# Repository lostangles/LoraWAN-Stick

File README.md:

# LoraWAN-Stick
PCB combining Atmega32u4, MTK3339 GPS module, and RN2903 LoraWAN module.

<a href="https://oshpark.com/shared_projects/d93rjKRX"></img></a>

# Functionality
I wanted to make a single PCB that had some GPIO, communication interfaces, a module to transmit LoraWAN packets, and a way to get current location.  The LoraWAN stack is offloaded from the 32u4 and rests in a PIC microcontroller inside the RN2903.  This allows a simple interface of simply passing the payload from the 32u4 to the RN2903 without having to worry about the LoraWAN stack inside your project.

The LoraWAN-Stick incorporates the LiPo charging circuitry common to the Adafruit Feather line of dev boards, as well as follows the same pinout for attachment of Adafruit Featherwings.  Because both the RN2903 and GPS module use serial communications, serial communications with other nodes may be difficult; the GPS module uses the hardware UART, and communication to the RN2903 uses software serial.  From my experience, having multiple software serial interfaces tends to work in unexpected ways, and should probably be avoided without thorough testing.

# Pins
Pinout follows Adafruit Feather format as I wanted to be able to add compatability of Adafruit Featherwings to this project.
The 32u4 only has a single hardware UART, hard wired to the TX/RX of the GPS module.  These pins are broken out on the header.

The RN2903 is controlled by serial, but because the 32u4 has only a single UART, a software serial interface must be used.  The RN2903 is hardwired with its RX on pin 5 and TX on pin 10.  Reset for the RN2903 is hard wired to pin 6 and should be pulled high when not in reset state.  The RN2903 Pickit3 programming header is also broken out to update the firmware on the RN2903 directly.

#uC Info
The 32u4-AU microcontroller that I used here comes preconfigured to use the internal oscillator, thus the C7, C8, and XTAL pads can be left empty.  When configuring the microcontroller for the first time, it will not show up as a USB device until the bootloader has been flashed to it via ISP.  Once the bootloader has been flashed, it should show up as an Adafruit Feather 32u4 under Device Manager, and can be programmed/configured in the same manner as any of the Adafruit 32u4 Feathers.

#Radio Interface
The RN2903 by default communicates on 56000 baud.  The SoftwareSerial library is more reliable at slower speeds; to set the baudrate in the RN2903, you must send a low signal on the TX line for at least two character lengths, followed by 0x55 at the new baudrate requested.  Using the Arduino libraries, this might look like:

```
digitalWrite(10, LOW);
delay(500);
digitalWrite(10, HIGH);
rn2903.begin(9600);
rn2903.write(0x55);
```

#Fuse Settings
The bootloader included configures the 32u4 in 8 MHz in the same configuration as the Adafruit 32u4 Feathers.
The uC can be configured to run with an internal oscillator or an external oscillator.  If you use the 32u4-AU variant, the built in oscillator can be used in lieu of an external oscillator.  The fuse settings to configure the uC as such would be something like:

`avrdude -c dragon_isp -p m32u4 -U lfuse:w:0xe2:m -U hfuse:w:0xd8:m -U efuse:w:0xfb:m -U flash:w:Caterina-Feather32u4.hex -v`

# Bill Of Materials
https://github.com/lostangles/LoraWAN-Stick/blob/master/LoraWAN-Stick.xlsx

Total cost: $52.52

U3	RN2903-I/RM095	RN2903-I_RM095:XCVR_RN2903-I%2fRM095	Microchip
U2	ATmega32U4-AU	Housings_QFP:TQFP-44_10x10mm_Pitch0.8mm	
U1	FGPMMOPA6H	FGPMMOPA6H:FGPMMOPA6H	
P1	USB_OTG	Connect:USB_Mini-B	
R1	22	Resistors_SMD:R_0603_HandSoldering	
R2	22	Resistors_SMD:R_0603_HandSoldering	
U4	SPX3819	adafruit:adafruit-SOT23-5L	
R3	100k	Resistors_SMD:R_0603_HandSoldering	
C1	10uF	Capacitors_SMD:C_0603_HandSoldering	
C2	10uF	Capacitors_SMD:C_0603_HandSoldering	
C3	1uF	Capacitors_SMD:C_0603_HandSoldering	
D1	DIODESCH	Diodes_SMD:D_0805	
CN1	JST_2PIN-SMT	adafruit:adafruit-JST-PH-2-SMT	
C4	1uF	Capacitors_SMD:C_0603_HandSoldering	
SW1	SPST	open-project:SW_PUSH_SMD	
U5	MCP73831	arthurc:SOT23-5	
D2	LED-BAT	Diodes_SMD:D_0805	
R4	1k	Resistors_SMD:R_0603_HandSoldering	
R5	10k	Resistors_SMD:R_0603_HandSoldering	
C5	10uF	Capacitors_SMD:C_0603_HandSoldering	
R6	100k	Resistors_SMD:R_0603_HandSoldering	
R7	100k	Resistors_SMD:R_0603_HandSoldering	
C6	10uF	Capacitors_SMD:C_0603_HandSoldering	
JP3	PINHD-1X12	adafruit:adafruit-1X12	
JP1	CONN_01X16	Pin_Headers:Pin_Header_Straight_1x16	
JP2	PINHD-1X6	adafruit:adafruit-1X06	
ANT1	CON-SMA	misc:CON-SMA-EDGE	
D3	LED-RED	Diodes_SMD:D_0805	
R8	1k	Resistors_SMD:R_0603_HandSoldering	
D4	LED-POW	Diodes_SMD:D_0805	
R9	1k	Resistors_SMD:R_0603_HandSoldering	

# TODO 

Add ICP header for 32u4

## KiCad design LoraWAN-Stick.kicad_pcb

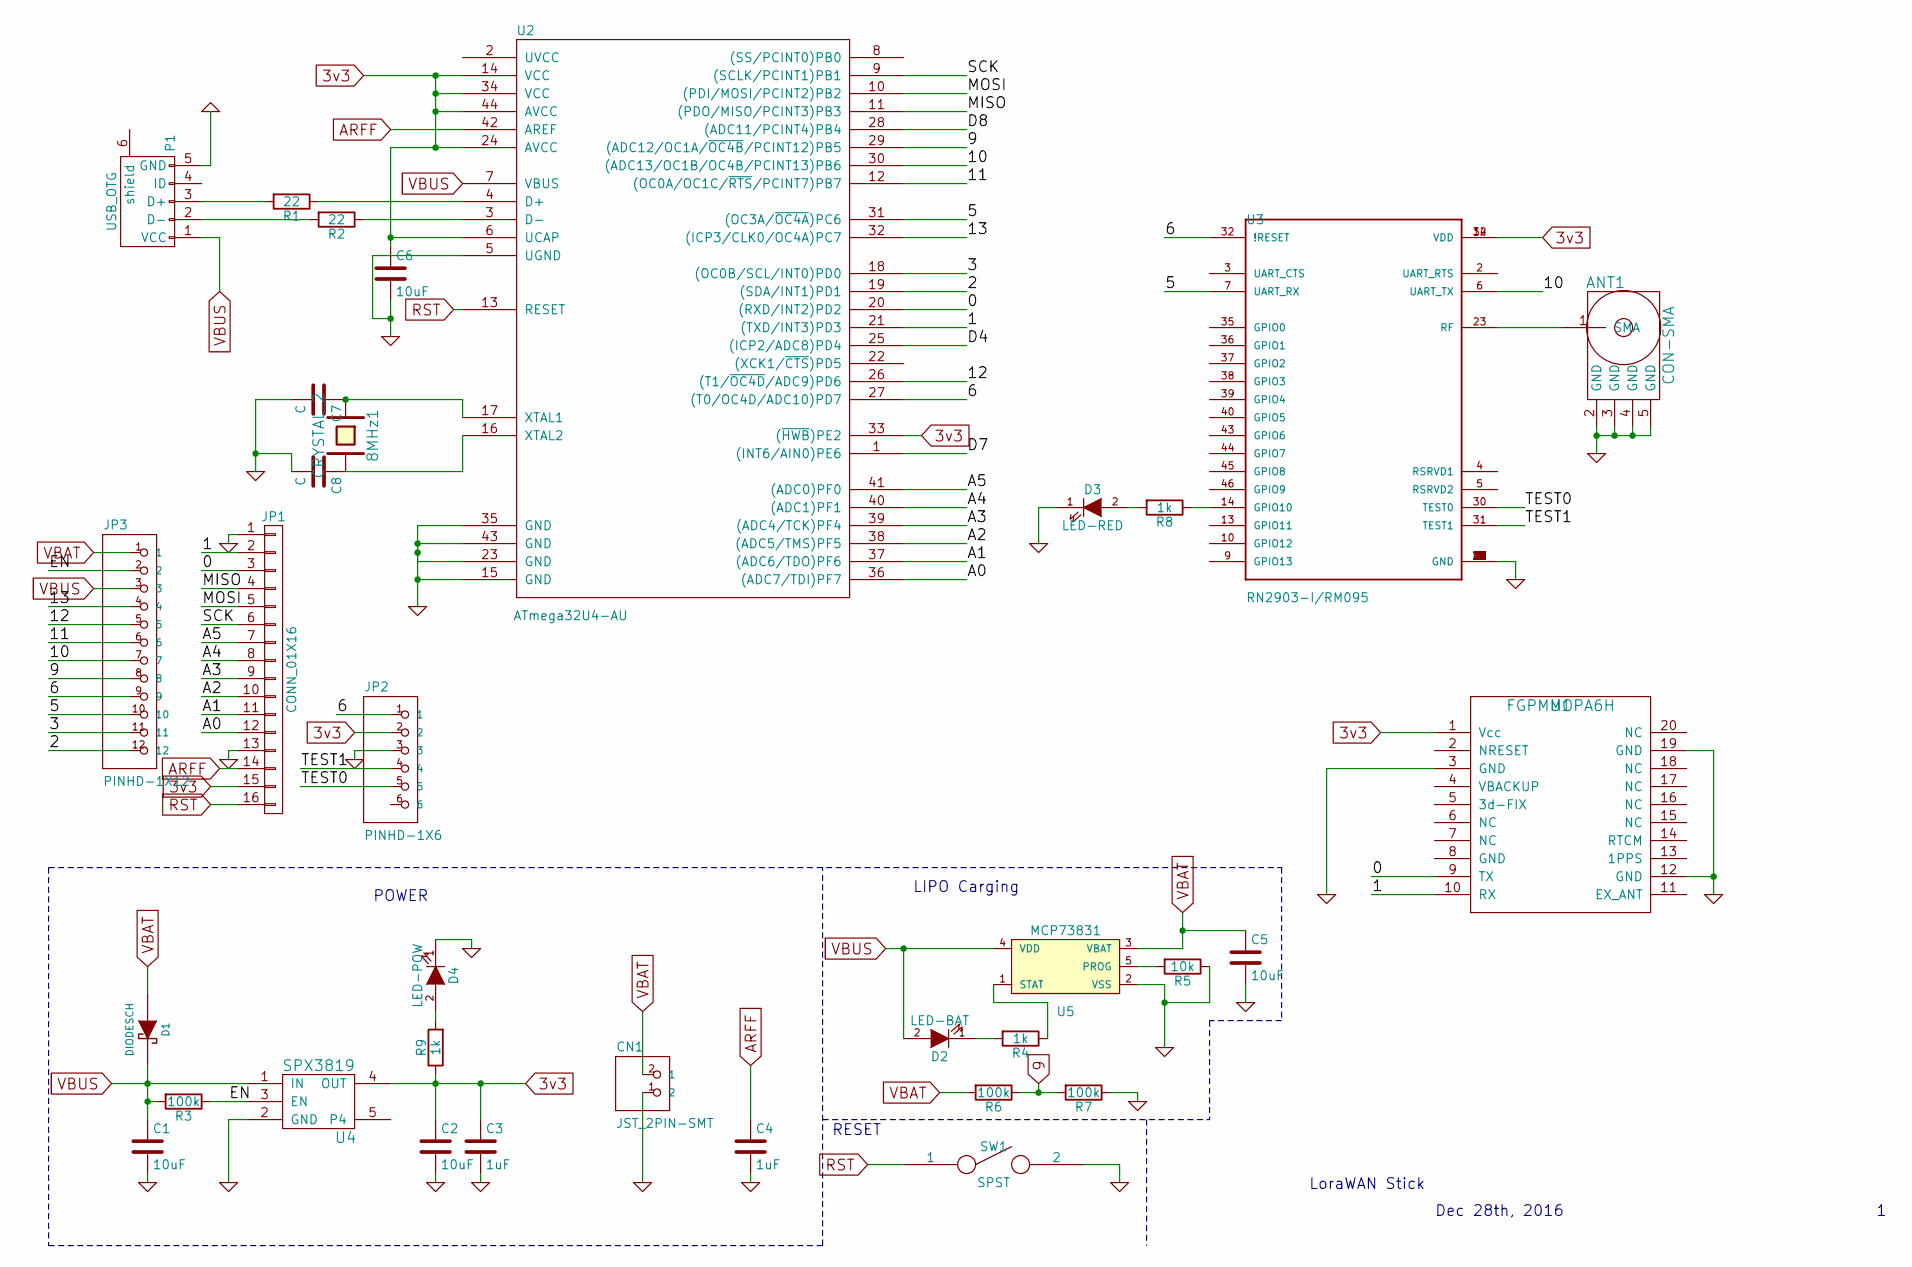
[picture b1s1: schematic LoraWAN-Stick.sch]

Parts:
8MHz1: CRYSTAL_2; ABM3
ANT1: CON-SMA; CON-SMA-EDGE
C1, C2, C5, C6: 10uF; C_0603_HandSoldering
C3, C4: 1uF; C_0603_HandSoldering
C7, C8: C; C_0603_HandSoldering
CN1: JST_2PIN-SMT; adafruit-JST-PH-2-SMT
D1: DIODESCH; D_0805
D2: LED-BAT; D_0805
D3: LED-RED; D_0805
D4: LED-POW; D_0805
JP1: CONN_01X16; Pin_Header_Straight_1x16
JP2: PINHD-1X6; adafruit-1X06
JP3: PINHD-1X12; adafruit-1X12
P1: USB_OTG; USB_Mini-B
R1, R2: 22; R_0603_HandSoldering
R3, R6, R7: 100k; R_0603_HandSoldering
R4, R8, R9: 1k; R_0603_HandSoldering
R5: 10k; R_0603_HandSoldering
SW1: SPST; SW_PUSH_SMD
U1: FGPMMOPA6H
U2: ATmega32U4-AU; TQFP-44_10x10mm_Pitch0.8mm
U3: RN2903-I/RM095; XCVR_RN2903-I%2fRM095
U4: SPX3819; adafruit-SOT23-5L
U5: MCP73831; SOT23-5

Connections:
3v3: C2.1, C3.1, C6.1, JP1.15, JP2.2, R9.1, U1.1 (Vcc), U2.6 (UCAP), U2.14 (VCC), U2.24 (AVCC), U2.33 ((~HWB~)PE2), U2.34 (VCC), U2.44 (AVCC), U3.12 (VDD), U3.34 (VDD), U4.4 (OUT)
9: JP3.8, R6.1, R7.2, U2.29 ((ADC12/OC1A/~OC4B~/PCINT12)PB5)
/0: JP1.3, U1.9 (TX), U2.20 ((RXD/INT2)PD2)
/1: JP1.2, U1.10 (RX), U2.21 ((TXD/INT3)PD3)
/2: JP3.12, U2.19 ((SDA/INT1)PD1)
/3: JP3.11, U2.18 ((OC0B/SCL/INT0)PD0)
/5: JP3.10, U2.31 ((OC3A/~OC4A~)PC6), U3.7 (UART_RX)
/6: JP2.1, JP3.9, U2.27 ((T0/OC4D/ADC10)PD7), U3.32 (!RESET)
/10: JP3.7, U2.30 ((ADC13/OC1B/OC4B/PCINT13)PB6), U3.6 (UART_TX)
/11: JP3.6, U2.12 ((OC0A/OC1C/~RTS~/PCINT7)PB7)
/12: JP3.5, U2.26 ((T1/~OC4D~/ADC9)PD6)
/13: JP3.4, U2.32 ((ICP3/CLK0/OC4A)PC7)
/A0: JP1.12, U2.36 ((ADC7/TDI)PF7)
/A1: JP1.11, U2.37 ((ADC6/TDO)PF6)
/A2: JP1.10, U2.38 ((ADC5/TMS)PF5)
/A3: JP1.9, U2.39 ((ADC4/TCK)PF4)
/A4: JP1.8, U2.40 ((ADC1)PF1)
/A5: JP1.7, U2.41 ((ADC0)PF0)
/D4: U2.25 ((ICP2/ADC8)PD4)
/D7: U2.1 ((INT6/AIN0)PE6)
/D8: U2.28 ((ADC11/PCINT4)PB4)
/EN: JP3.2, R3.1, U4.3 (EN)
/MISO: JP1.4, U2.11 ((PDO/MISO/PCINT3)PB3)
/MOSI: JP1.5, U2.10 ((PDI/MOSI/PCINT2)PB2)
/SCK: JP1.6, U2.9 ((SCLK/PCINT1)PB1)
/TEST0: JP2.5, U3.30 (TEST0)
/TEST1: JP2.4, U3.31 (TEST1)
ARFF: C4.1, JP1.14, U2.42 (AREF)
GND: ANT1.2 (GND), ANT1.3 (GND), ANT1.4 (GND), ANT1.5 (GND), C1.2, C2.2, C3.2, C4.2, C5.2, C6.2, C7.2, C8.2, CN1.1 (2), D3.1 (K), D4.1 (K), JP1.1, JP1.13, JP2.3, P1.5 (GND), R5.1, R7.1, SW1.2, U1.3 (GND), U1.12 (GND), U1.19 (GND), U2.5 (UGND), U2.15 (GND), U2.23 (GND), U2.35 (GND), U2.43 (GND), U3.1 (GND), U3.8 (GND), U3.11 (GND), U3.20 (GND), U3.21 (GND), U3.22 (GND), U3.24 (GND), U3.26 (GND), U3.27 (GND), U3.28 (GND), U3.33 (GND), U3.41 (GND), U3.47 (GND), U4.2 (GND), U5.2 (VSS)
unnamed: 8MHz1.1, C7.1, U2.17 (XTAL1)
unnamed: 8MHz1.2, C8.1, U2.16 (XTAL2)
unnamed: ANT1.1 (SMA), U3.23 (RF)
unnamed: D2.1 (K), R4.2
unnamed: D3.2 (A), R8.2
unnamed: D4.2 (A), R9.2
unnamed: P1.2 (D-), R2.2
unnamed: P1.3 (D+), R1.2
unnamed: R1.1, U2.4 (D+)
unnamed: R2.1, U2.3 (D-)
unnamed: R4.1, U5.1 (STAT)
unnamed: R5.2, U5.5 (PROG)
unnamed: R8.1, U3.14 (GPIO10)
RST: JP1.16, SW1.1, U2.13 (RESET)
VBAT: C5.1, CN1.2 (1), D1.1 (A), JP3.1, R6.2, U5.3 (VBAT)
VBUS: C1.1, D1.2 (K), D2.2 (A), JP3.3, P1.1 (VCC), R3.2, U2.7 (VBUS), U4.1 (IN), U5.4 (VDD)

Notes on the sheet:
POWER
RESET
LIPO Carging
LoraWAN Stick
Dec 28th, 2016

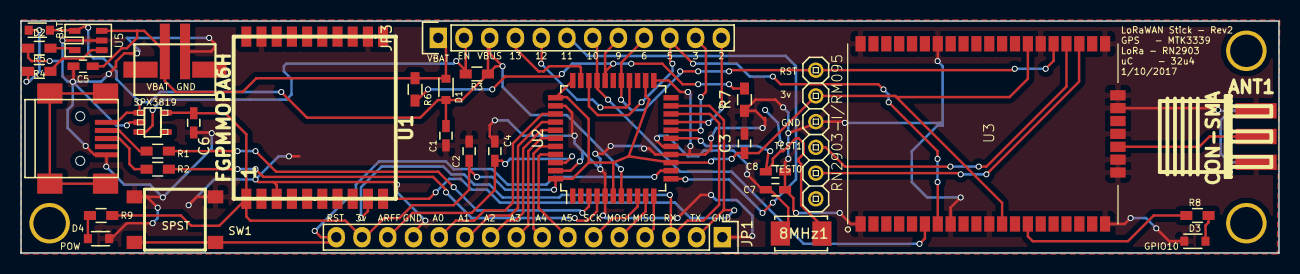
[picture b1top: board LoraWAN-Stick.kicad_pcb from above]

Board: 2 copper layers, 124.1 x 22.9 mm, 34 parts (0 on the bottom side), 42 nets.

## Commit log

2016-12-28 :tada: Added .gitattributes
2016-12-28 Initial commit
    Initial commit
2016-12-29 Updated BOM with price + links
2017-01-15 Fixed LiPo charging, added holes on edges, added pads for external crystal, cleaned up silk screen
2017-01-15 Rev2
    Fixed LiPo charging, added holes on edges, added pads for external
    crystal, cleaned up silk screen
2017-01-15 Fixed PCB image
2017-01-26 Added bootloader
